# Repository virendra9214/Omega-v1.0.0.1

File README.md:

Omega – ESP32 STEM Controller Board

Omega is an ESP32-based controller board created by  VIRENDRA SINGH SHEKHAWAT from India to make STEM education, robotics, and IoT more accessible.  
It combines Wi-Fi, BLE, sensor inputs, motor drivers, and easy expansion in one compact design — perfect for classrooms, tinkering labs, hobbyists, and competitions.

---

Key Features
- MCU: ESP32-WROOM-32E (Dual-core, Wi-Fi + BLE)
- Programming: Arduino IDE, MicroPython, block-based IDE (PictoBlox-style)
- Motors & Servos:
  - 2× TB6612FNG motor drivers (up to 4 12v motors)
  - 3× Servo headers (5 V PWM)
- Sensors Supported:
  - Ultrasonic, IR, MPU6050 IMU, Color sensor, DHT, analog/digital expansion
- Outputs:
  - WS2812B RGB LED
  - PAM8403 speaker amplifier
- Connectivity:
  - I²C, UART, PWM, ADC, DAC via JST connectors
- Power:
  - Auto USB-C / 12 V barrel jack switching (FDN340P MOSFET)
  - Onboard 5 V & 3.3 V regulation with fuse, diodes, ESD protection

---

 Educational Value
- Free for students, hobbyists, and individual educators.
- Supports hands-on STEM learning: electronics, coding, IoT, robotics
- Beginner-friendly with block-based coding
- Expandable for advanced learners with C++/Python
- Supports Indian education initiatives (NEP 2020, Skill India, Atal Tinkering Labs)

---

Example Projects
- IoT-based smart irrigation system  
- Accident detection and car safety module  
- Line follower / obstacle avoiding robots  
- BLE remote-controlled car  
- Classroom experiments: data logging, servo control, LED patterns  

---

 Repository Contents
- `/Production` → KiCad schematic, PCB, BOM  
- `/firmware` → Arduino / MicroPython example codes  
- `/datasheets` → Datasheets, pin mapping, tutorials  
- `/codes` → Ready-to-run projects for students and testing after production 

---

License
This project is released under the Omega Educational License (OEL-1.0).  
-  Free for education, research, and personal use  
-  Commercial use requires a paid license from the creator  
-  Significant design modifications and redistributions are not allowed  
youtube link:https://www.youtube.com/@LEARN_OMEGA
📩 Contact: virendrasinghshekhawat786@gmail.com for commercial licensing inquiries.

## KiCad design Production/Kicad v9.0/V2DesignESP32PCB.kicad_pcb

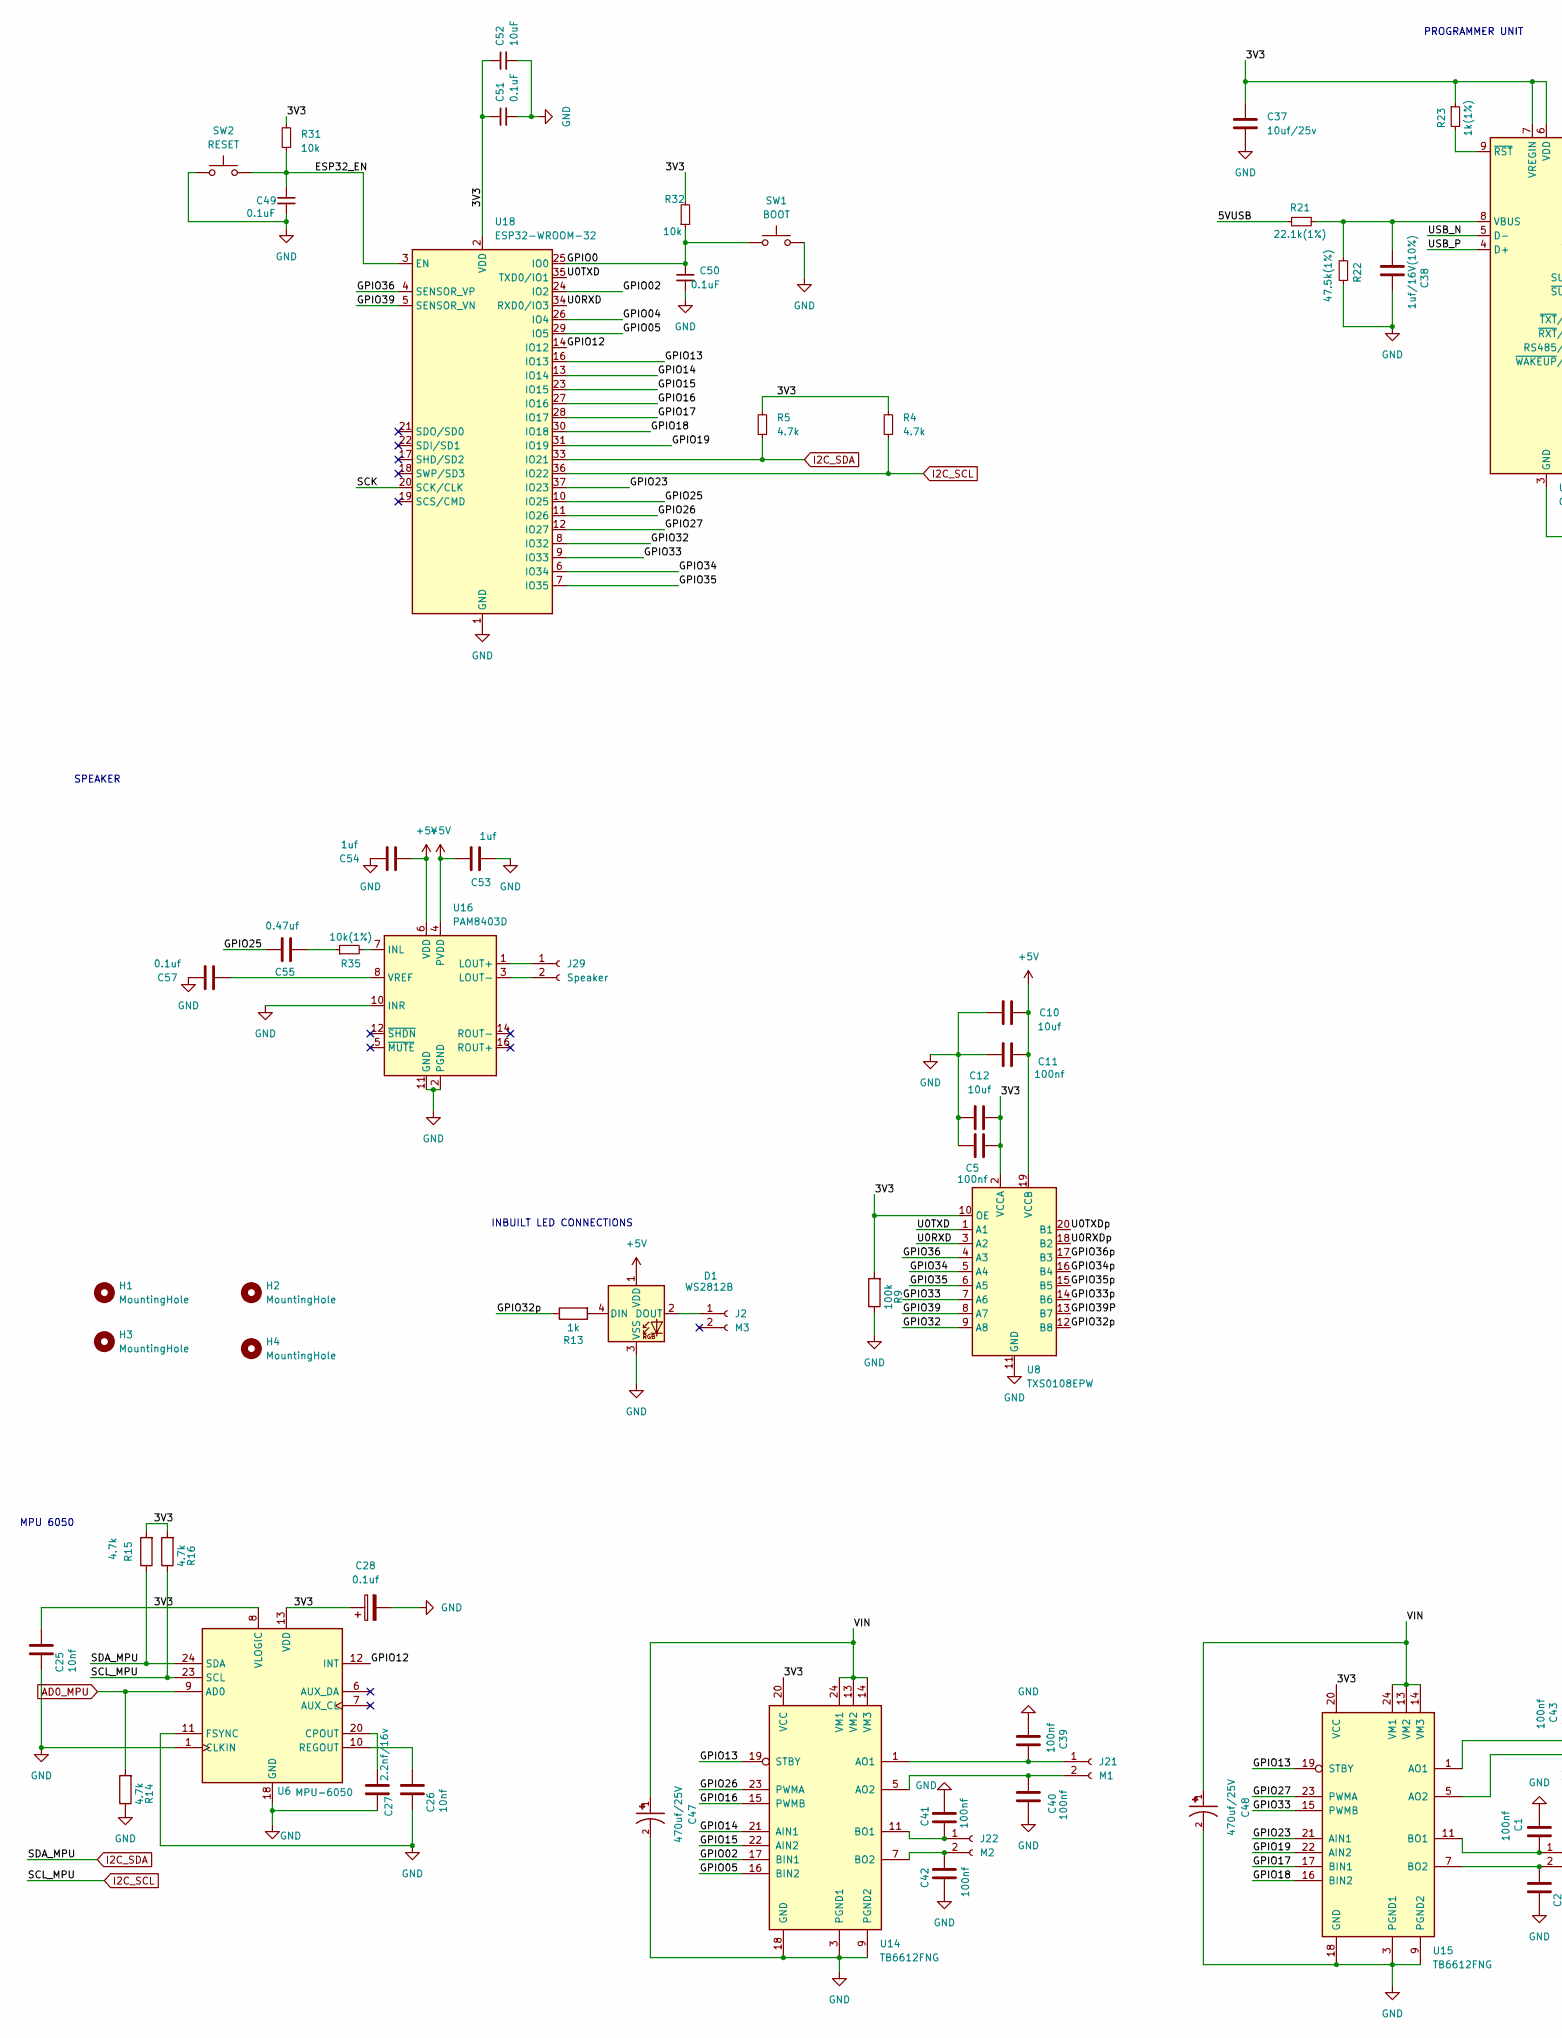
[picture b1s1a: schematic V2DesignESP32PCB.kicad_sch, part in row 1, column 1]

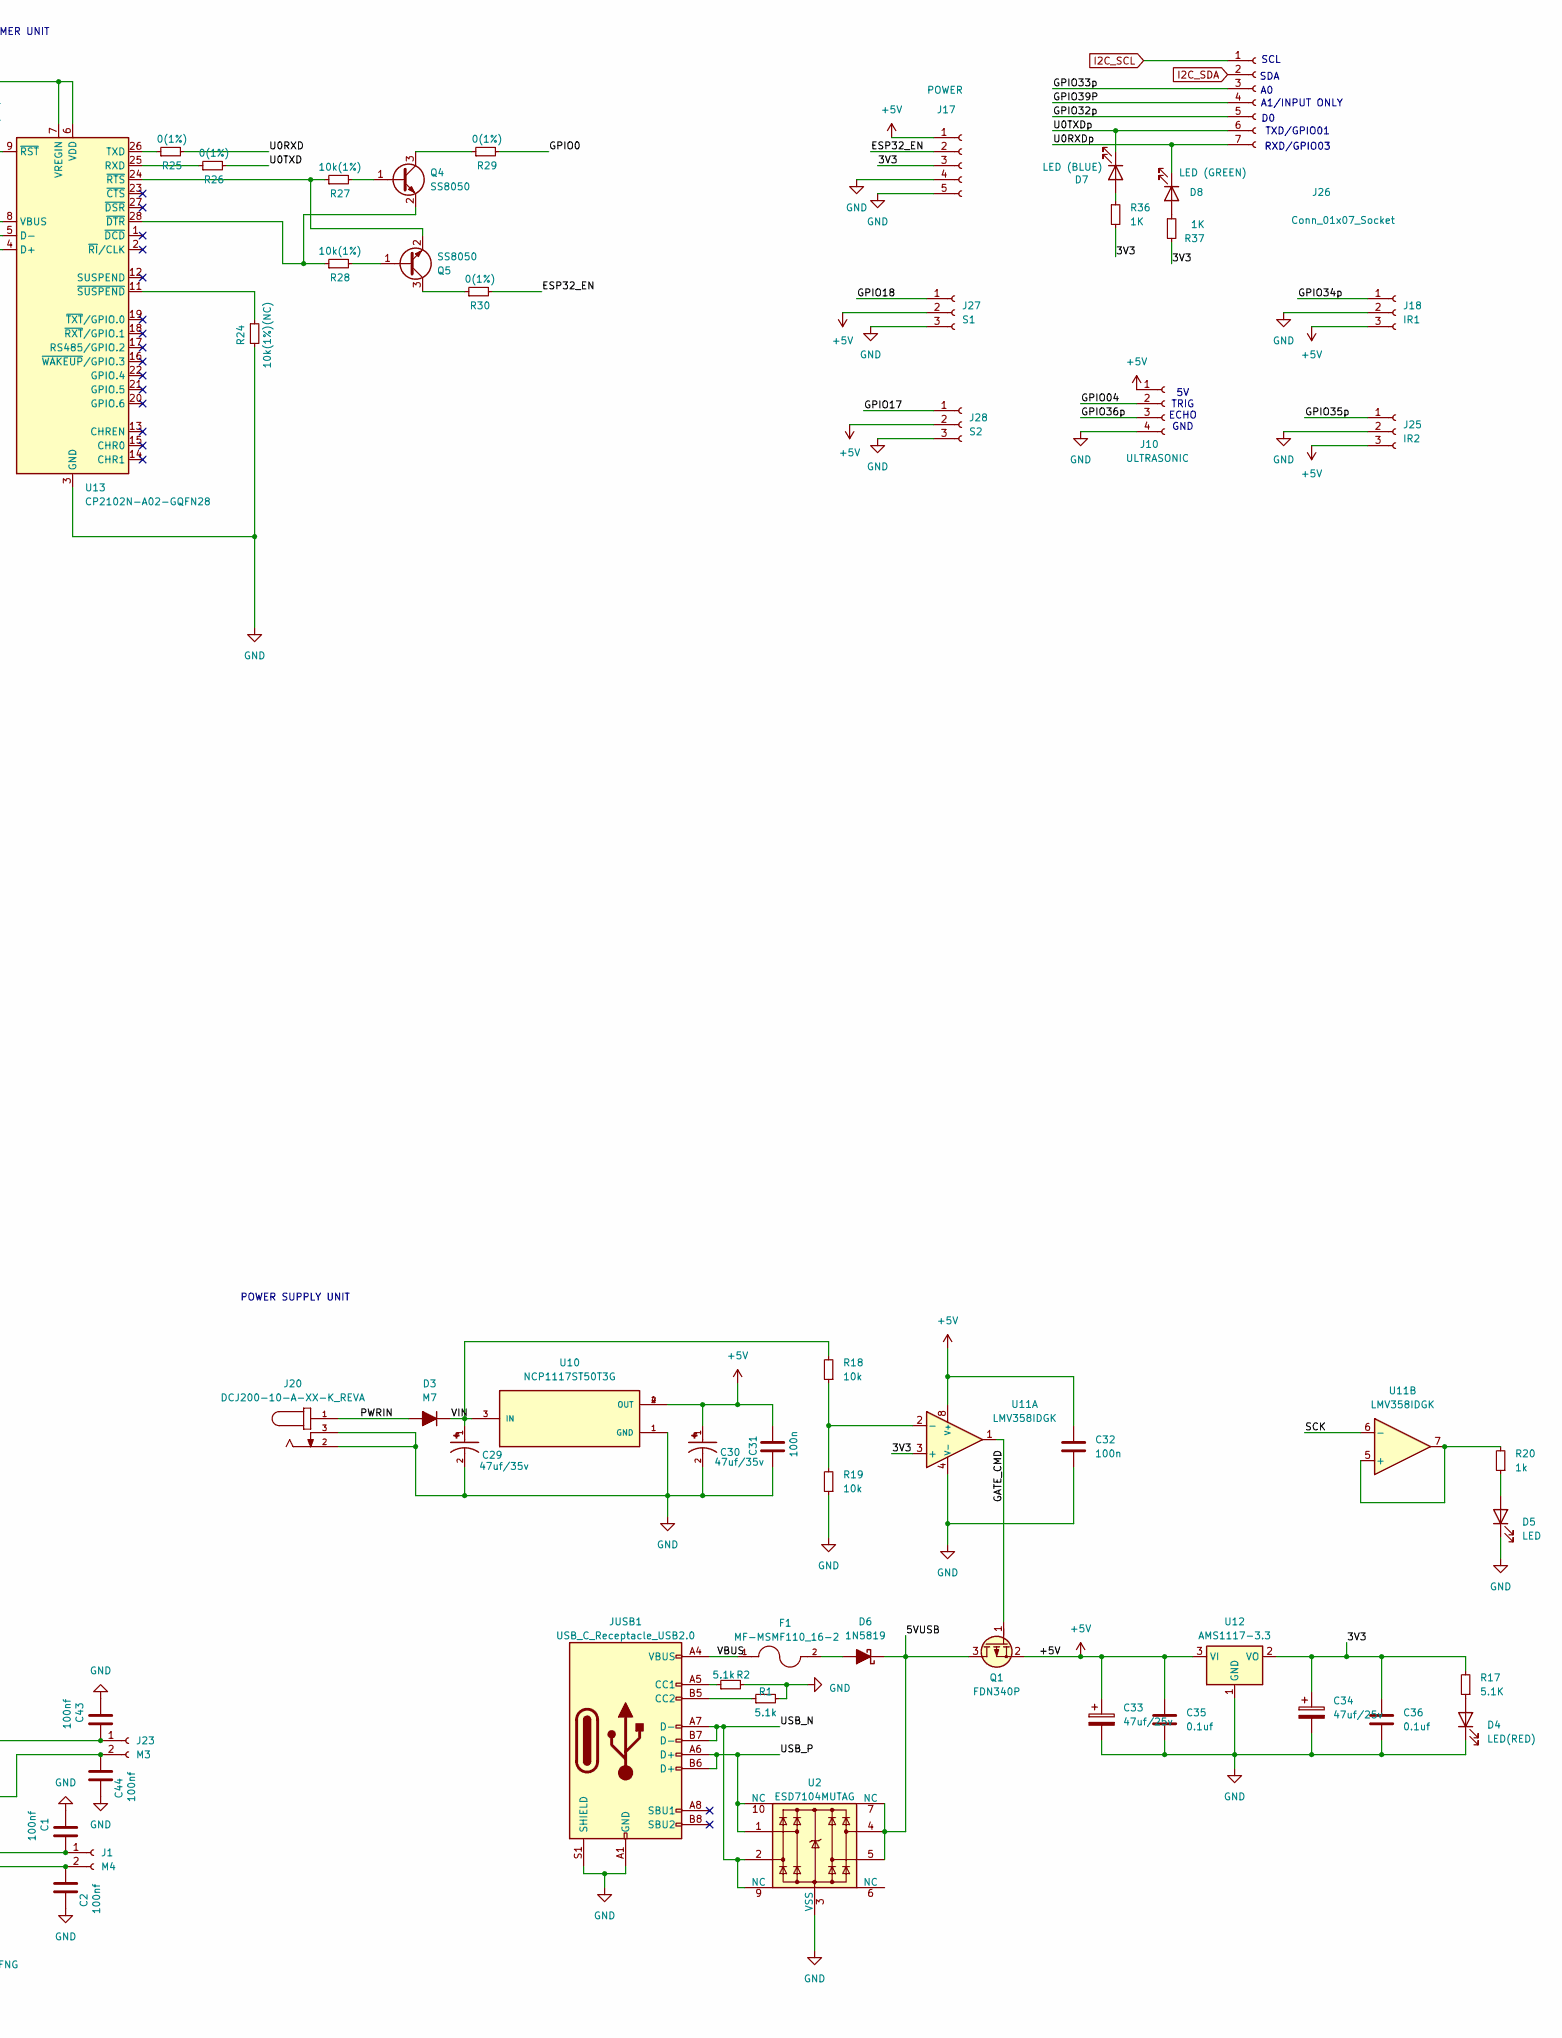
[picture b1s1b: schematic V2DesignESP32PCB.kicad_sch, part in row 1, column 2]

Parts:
C1, C2, C5, C11, C39, C40, C41, C42, C43, C44: 100nf; C_0805_2012Metric
C10, C12: 10uf; C_0805_2012Metric
C25, C26: 10nf; C_0603_1608Metric
C27: 2.2nf/16v; C_0603_1608Metric
C28: 0.1uf; C_0603_1608Metric
C29, C30: 47uf/35v; CAP_EEETC1V470V; PARTREV 10-Oct-19
C31, C32: 100n; C_0805_2012Metric
C33, C34: 47uf/25v; C_0805_2012Metric
C35, C36, C57: 0.1uf; C_0805_2012Metric
C37: 10uf/25v; C_0603_1608Metric
C38: 1uf/16V(10%); C_0603_1608Metric
C47, C48: 470uf/25V; CAP_EEETC1V470V; PARTREV 10-Oct-19
C49, C50, C51: 0.1uF; C_0603_1608Metric; MANUFECTURER PART NUMBER ${ITEM_NUMBER}
C52: 10uF; C_0603_1608Metric; MANUFECTURER PART NUMBER ${ITEM_NUMBER}
C53, C54: 1uf; C_0805_2012Metric
C55: 0.47uf; C_0805_2012Metric
D1: WS2812B; LED_WS2812B_PLCC4_5.0x5.0mm_P3.2mm; MANUFECTURER PART NUMBER ${ITEM_NUMBER}
D3: M7; D_SMA
D4: LED(RED); LED_0805_2012Metric; MANUFECTURER PART NUMBER ${ITEM_NUMBER}
D5: LED; LED_0805_2012Metric; MANUFECTURER PART NUMBER ${ITEM_NUMBER}
D6: 1N5819; D_SOD-123
D7: LED (BLUE); LED_0805_2012Metric; MANUFECTURER PART NUMBER ${ITEM_NUMBER}
D8: LED (GREEN); LED_0805_2012Metric; MANUFECTURER PART NUMBER ${ITEM_NUMBER}
F1: MF-MSMF110_16-2; FUSER_MF-MSMF110_16-2
H1, H2, H3, H4: MountingHole; MountingHole_4mm
J1: M4; MANUFECTURER PART NUMBER ${ITEM_NUMBER}
J2, J23: M3; JST_EH_B2B-EH-A_1x02_P2.50mm_Vertical; MANUFECTURER PART NUMBER ${ITEM_NUMBER}
J10: ULTRASONIC; JST_EH_B4B-EH-A_1x04_P2.50mm_Vertical; MANUFECTURER PART NUMBER ${ITEM_NUMBER}
J17: POWER; JST_EH_B5B-EH-A_1x05_P2.50mm_Vertical
J18: IR1; JST_EH_B3B-EH-A_1x03_P2.50mm_Vertical; MANUFECTURER PART NUMBER ${ITEM_NUMBER}
J20: DCJ200-10-A-XX-K_REVA; BarrelJack_GCT_DCJ200-10-A_Horizontal; PARTREV A
J21: M1; JST_EH_B2B-EH-A_1x02_P2.50mm_Vertical; MANUFECTURER PART NUMBER ${ITEM_NUMBER}
J22: M2; JST_EH_B2B-EH-A_1x02_P2.50mm_Vertical; MANUFECTURER PART NUMBER ${ITEM_NUMBER}
J25: IR2; JST_EH_B3B-EH-A_1x03_P2.50mm_Vertical; MANUFECTURER PART NUMBER ${ITEM_NUMBER}
J26: Conn_01x07_Socket; JST_EH_B7B-EH-A_1x07_P2.50mm_Vertical
J27: S1; JST_EH_B3B-EH-A_1x03_P2.50mm_Vertical; MANUFECTURER PART NUMBER ${ITEM_NUMBER}
J28: S2; JST_EH_B3B-EH-A_1x03_P2.50mm_Vertical; MANUFECTURER PART NUMBER ${ITEM_NUMBER}
J29: Speaker; JST_EH_B2B-EH-A_1x02_P2.50mm_Vertical; MANUFECTURER PART NUMBER ${ITEM_NUMBER}
JUSB1: USB_C_Receptacle_USB2.0; USB_C_Receptacle_GCT_USB4105-xx-A_16P_TopMnt_Horizontal; MANUFECTURER PART NUMBER ${ITEM_NUMBER}
Q1: FDN340P; SuperSOT-3
Q4, Q5: SS8050; SOT-23
R1, R2: 5.1k; R_0805_2012Metric; MANUFECTURER PART NUMBER ${ITEM_NUMBER}
R4, R5: 4.7k; R_0603_1608Metric; MANUFECTURER PART NUMBER ${ITEM_NUMBER}
R9: 100k; R_0603_1608Metric
R13: 1k; R_0603_1608Metric
R14, R15, R16: 4.7k; R_0603_1608Metric
R17: 5.1K; R_0805_2012Metric; MANUFECTURER PART NUMBER ${ITEM_NUMBER}
R18, R19: 10k; R_0805_2012Metric; MANUFECTURER PART NUMBER ${ITEM_NUMBER}
R20: 1k; R_0805_2012Metric; MANUFECTURER PART NUMBER ${ITEM_NUMBER}
R21: 22.1k(1%); R_0603_1608Metric; MANUFECTURER PART NUMBER ${ITEM_NUMBER}
R22: 47.5k(1%); R_0603_1608Metric; MANUFECTURER PART NUMBER ${ITEM_NUMBER}
R23: 1k(1%); R_0603_1608Metric; MANUFECTURER PART NUMBER ${ITEM_NUMBER}
R24: 10k(1%)(NC); R_0603_1608Metric; MANUFECTURER PART NUMBER ${ITEM_NUMBER}
R25, R26, R29, R30: 0(1%); R_0603_1608Metric; MANUFECTURER PART NUMBER ${ITEM_NUMBER}
R27, R28: 10k(1%); R_0603_1608Metric; MANUFECTURER PART NUMBER ${ITEM_NUMBER}
R31, R32: 10k; R_0603_1608Metric; MANUFECTURER PART NUMBER ${ITEM_NUMBER}
R35: 10k(1%); R_0805_2012Metric; MANUFECTURER PART NUMBER ${ITEM_NUMBER}
R36, R37: 1K; R_0805_2012Metric; MANUFECTURER PART NUMBER ${ITEM_NUMBER}
SW1: BOOT; SW_SPST_PTS810
SW2: RESET; SW_SPST_PTS810
U2: ESD7104MUTAG; Diodes_UDFN-10_1.0x2.5mm_P0.5mm; MANUFECTURER PART NUMBER ${ITEM_NUMBER}
U6: MPU-6050; InvenSense_QFN-24_4x4mm_P0.5mm
U8: TXS0108EPW; TSSOP-20_4.4x6.5mm_P0.65mm
U10: NCP1117ST50T3G; SOT230P700X180-4N; DigiKey_Part_Number NCP1117ST50T3GOSTR-ND
U11: LMV358IDGK; MSOP-8_3x3mm_P0.65mm
U12: AMS1117-3.3; SOT-223-3_TabPin2
U13: CP2102N-A02-GQFN28; QFN-28-1EP_5x5mm_P0.5mm_EP3.35x3.35mm
U14, U15: TB6612FNG; SSOP-24_5.3x8.2mm_P0.65mm
U16: PAM8403D; SOP-16_3.9x9.9mm_P1.27mm
U18: ESP32-WROOM-32

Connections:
+5V: C10.2, C11.1, C30.1, C31.1, C32.1, C33.1, C35.1, C53.2, C54.1, D1.1 (VDD), J10.1, J17.1, J18.3, J25.3, J27.2, J28.2, Q1.2 (S), U8.19 (VCCB), U10.2 (OUT), U10.4 (OUT), U11.8 (V+), U12.3 (VI), U16.4 (PVDD), U16.6 (VDD), U16.13 (PVDD)
/3V3: C5.1, C12.2, C25.1, C28.1, C34.1, C36.1, C37.1, C51.1, C52.1, J17.3, R4.2, R5.2, R9.2, R15.2, R16.2, R17.2, R23.1, R31.2, R32.2, R36.2, R37.2, U6.8 (VLOGIC), U6.13 (VDD), U8.2 (VCCA), U8.10 (OE), U11.3 (+), U12.2 (VO), U13.6 (VDD), U13.7 (VREGIN), U14.20 (VCC), U15.20 (VCC), U18.2 (VDD)
/5VUSB: D6.1 (K), Q1.3 (D), R21.2, U2.4, U2.5, U2.7 (NC)
/ESP32_EN: C49.1, J17.2, R30.2, R31.1, SW2.2, U18.3 (EN)
/GATE_CMD: Q1.1 (G), U11.1
/GPIO0: C50.1, R29.2, R32.1, SW1.1, U18.25 (IO0)
/GPIO02: U14.17 (BIN1), U18.24 (IO2)
/GPIO04: J10.2, U18.26 (IO4)
/GPIO05: U14.16 (BIN2), U18.29 (IO5)
/GPIO12: U6.12 (INT), U18.14 (IO12)
/GPIO13: U14.19 (STBY), U15.19 (STBY), U18.16 (IO13)
/GPIO14: U14.21 (AIN1), U18.13 (IO14)
/GPIO15: U14.22 (AIN2), U18.23 (IO15)
/GPIO16: U14.15 (PWMB), U18.27 (IO16)
/GPIO17: J28.1, U15.17 (BIN1), U18.28 (IO17)
/GPIO18: J27.1, U15.16 (BIN2), U18.30 (IO18)
/GPIO19: U15.22 (AIN2), U18.31 (IO19)
/GPIO23: U15.21 (AIN1), U18.37 (IO23)
/GPIO25: C55.2, U18.10 (IO25)
/GPIO26: U14.23 (PWMA), U18.11 (IO26)
/GPIO27: U15.23 (PWMA), U18.12 (IO27)
/GPIO32: U8.9 (A8), U18.8 (IO32)
/GPIO32p: J26.5, R13.1, U8.12 (B8)
/GPIO33: U8.7 (A6), U15.15 (PWMB), U18.9 (IO33)
/GPIO33p: J26.3, U8.14 (B6)
/GPIO34: U8.5 (A4), U18.6 (IO34)
/GPIO34p: J18.1, U8.16 (B4)
/GPIO35: U8.6 (A5), U18.7 (IO35)
/GPIO35p: J25.1, U8.15 (B5)
/GPIO36: U8.4 (A3), U18.4 (SENSOR_VP)
/GPIO36p: J10.3, U8.17 (B3)
/GPIO39: U8.8 (A7), U18.5 (SENSOR_VN)
/GPIO39P: J26.4, U8.13 (B7)
/PWRIN: D3.2 (A), J20.1
/SCK: U11.6 (-), U18.20 (SCK/CLK)
/U0RXD: R25.2, U8.3 (A2), U18.34 (RXD0/IO3)
/U0RXDp: D8.1 (K), J26.7, U8.18 (B2)
/U0TXD: R26.2, U8.1 (A1), U18.35 (TXD0/IO1)
/U0TXDp: D7.1 (K), J26.6, U8.20 (B1)
/USB_N: JUSB1.A7 (D-), JUSB1.B7 (D-), U2.2, U2.9 (NC), U13.5 (D-)
/USB_P: JUSB1.A6 (D+), JUSB1.B6 (D+), U2.1, U2.10 (NC), U13.4 (D+)
/VBUS: F1.1, JUSB1.A4 (VBUS), JUSB1.A9 (VBUS), JUSB1.B4 (VBUS), JUSB1.B9 (VBUS)
/VIN: C29.1, C47.1, C48.1, D3.1 (K), R18.2, U10.3 (IN), U14.13 (VM2), U14.14 (VM3), U14.24 (VM1), U15.13 (VM2), U15.14 (VM3), U15.24 (VM1)
AD0_MPU: R14.2, U6.9 (AD0)
GND: C1.2, C2.2, C5.2, C10.1, C11.2, C12.1, C25.2, C26.2, C27.2, C28.2, C29.2, C30.2, C31.2, C32.2, C33.2, C34.2, C35.2, C36.2, C37.2, C38.2, C39.2, C40.2, C41.2, C42.2, C43.2, C44.2, C47.2, C48.2, C49.2, C50.2, C51.2, C52.2, C53.1, C54.2, C57.2, D1.3 (VSS), D4.1 (K), D5.1 (K), J10.4, J17.4, J17.5, J18.2, J20.2, J20.3, J25.2, J27.3, J28.3, JUSB1.A1 (GND), JUSB1.A12 (GND), JUSB1.B1 (GND), JUSB1.B12 (GND), JUSB1.S1 (SHIELD), R1.2, R2.2, R9.1, R14.1, R19.1, R22.1, R24.2, SW1.2, SW2.1, U2.3 (VSS), U2.8 (VSS), U6.1 (CLKIN), U6.11 (FSYNC), U6.18 (GND), U8.11 (GND), U10.1 (GND), U11.4 (V-), U12.1 (GND), U13.3 (GND), U13.29 (GND), U14.3 (PGND1), U14.4 (PGND1), U14.9 (PGND2), U14.10 (PGND2), U14.18 (GND), U15.3 (PGND1), U15.4 (PGND1), U15.9 (PGND2), U15.10 (PGND2), U15.18 (GND), U16.2 (PGND), U16.10 (INR), U16.11 (GND), U16.15 (PGND), U18.1 (GND), U18.15 (GND), U18.38 (GND), U18.39 (GND)
I2C_SCL: J26.1, R4.1, R16.1, U6.23 (SCL), U18.36 (IO22)
I2C_SDA: J26.2, R5.1, R15.1, U6.24 (SDA), U18.33 (IO21)
unnamed: C55.1, R35.1
unnamed: D1.4 (DIN), R13.2
unnamed: D1.2 (DOUT), J2.1
unnamed: D4.2 (A), R17.1
unnamed: D5.2 (A), R20.1
unnamed: D6.2 (A), F1.2
unnamed: D7.2 (A), R36.1
unnamed: D8.2 (A), R37.1
unnamed: C1.1, J1.1, U15.11 (BO1), U15.12 (BO1)
unnamed: C2.1, J1.2, U15.7 (BO2), U15.8 (BO2)
unnamed: C39.1, J21.1, U14.1 (AO1), U14.2 (AO1)
unnamed: C40.1, J21.2, U14.5 (AO2), U14.6 (AO2)
unnamed: C41.1, J22.1, U14.11 (BO1), U14.12 (BO1)
unnamed: C42.1, J22.2, U14.7 (BO2), U14.8 (BO2)
unnamed: C43.1, J23.1, U15.1 (AO1), U15.2 (AO1)
unnamed: C44.1, J23.2, U15.5 (AO2), U15.6 (AO2)
unnamed: J29.1, U16.1 (LOUT+)
unnamed: J29.2, U16.3 (LOUT-)
unnamed: JUSB1.A5 (CC1), R2.1
unnamed: JUSB1.B5 (CC2), R1.1
unnamed: Q4.1 (B), R27.2
unnamed: Q4.3 (C), R29.1
unnamed: Q4.2 (E), R28.1, U13.28 (~DTR)
unnamed: Q5.1 (B), R28.2
unnamed: Q5.3 (C), R30.1
unnamed: Q5.2 (E), R27.1, U13.24 (~RTS)
unnamed: C27.1, U6.20 (CPOUT)
unnamed: C26.1, U6.10 (REGOUT)
unnamed: R18.1, R19.2, U11.2 (-)
unnamed: R20.2, U11.5 (+), U11.7
unnamed: R26.1, U13.25 (RXD)
unnamed: R25.1, U13.26 (TXD)
unnamed: C38.1, R21.1, R22.2, U13.8 (VBUS)
unnamed: R23.2, U13.9 (~RST)
unnamed: R24.1, U13.11 (~SUSPEND)
unnamed: R35.2, U16.7 (INL)
unnamed: C57.1, U16.8 (VREF)

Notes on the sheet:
PROGRAMMER UNIT
SCL
MPU 6050
INBUILT LED CONNECTIONS
A1/INPUT ONLY
SDA
5V TRIG ECHO GND
POWER SUPPLY UNIT
RXD/GPIO03
SPEAKER
TXD/GPIO01

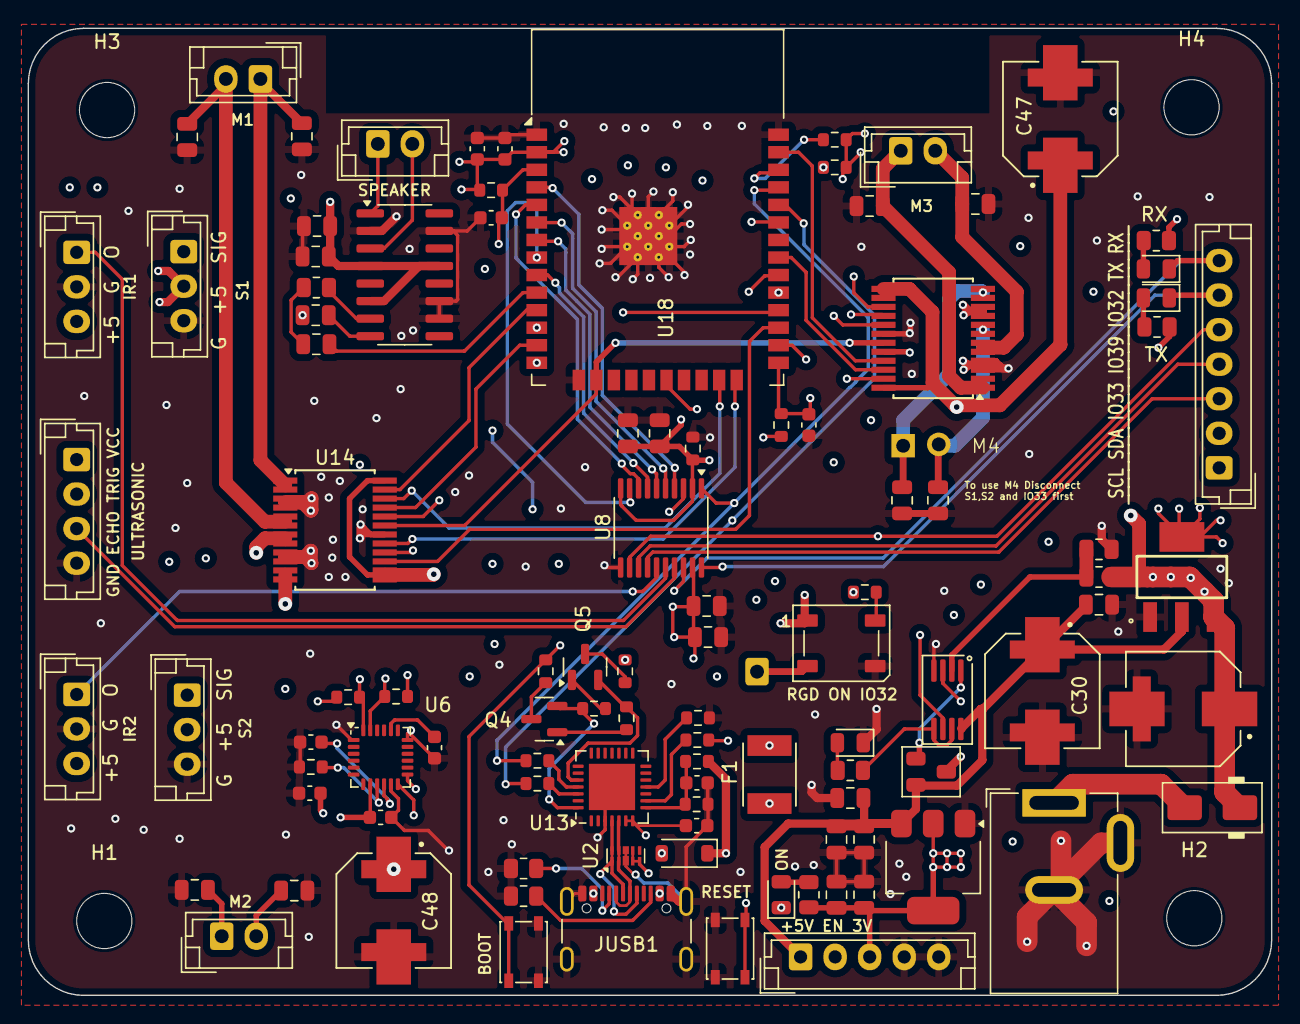
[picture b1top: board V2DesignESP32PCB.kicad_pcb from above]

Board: 4 copper layers, 90.0 x 70.0 mm, 105 parts (0 on the bottom side), 83 nets.

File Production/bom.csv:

Designator,Footprint,Quantity,Value,LCSC Part #
"_3, _2, ",,3,,
"C1, C11, C2, C39, C40, C41, C42, C43, C44, C5",0805,10,100nf,
"C10, C12",0805,2,10uf,
"C25, C26",0603,2,10nf,
C27,0603,1,2.2nf/16v,
"C28, C49, C50, C51",0603,4,0.1uf,
"C29, C30",CAP_EEETC1V470V,2,47uf/35v,
"C31, C32",0805,2,100n,
"C33, C34",0805,2,47uf/25v,
"C35, C36, C57",0805,3,0.1uf,
C37,0603,1,10uf/25v,
C38,0603,1,1uf/16V(10%),
"C47, C48",CAP_EEETC1V470V,2,470uf/25V,
C52,0603,1,10uF,
"C53, C54",0805,2,1uf,
C55,0805,1,0.47uf,
D1,LED_WS2812B_PLCC4_5.0x5.0mm_P3.2mm,1,WS2812B,
D3,D_SMA,1,M7,
D4,0805,1,LED(RED),
D5,0805,1,LED,
D6,D_SOD-123,1,1N5819,
D7,0805,1,LED (BLUE),
D8,0805,1,LED (GREEN),
F1,FUSER_MF-MSMF110_16-2,1,MF-MSMF110_16-2,
J10,JST_EH_B4B-EH-A_1x04_P2.50mm_Vertical,1,ULTRASONIC,
J17,JST_EH_B5B-EH-A_1x05_P2.50mm_Vertical,1,POWER,
J18,JST_EH_B3B-EH-A_1x03_P2.50mm_Vertical,1,IR1,
J20,BarrelJack_GCT_DCJ200-10-A_Horizontal,1,DCJ200-10-A-XX-K_REVA,
J21,JST_EH_B2B-EH-A_1x02_P2.50mm_Vertical,1,M1,
J22,JST_EH_B2B-EH-A_1x02_P2.50mm_Vertical,1,M2,
J23,JST_EH_B2B-EH-A_1x02_P2.50mm_Vertical,1,M3,
J25,JST_EH_B3B-EH-A_1x03_P2.50mm_Vertical,1,IR2,
J26,JST_EH_B7B-EH-A_1x07_P2.50mm_Vertical,1,Conn_01x07_Socket,
J27,JST_EH_B3B-EH-A_1x03_P2.50mm_Vertical,1,S1,
J28,JST_EH_B3B-EH-A_1x03_P2.50mm_Vertical,1,S2,
J29,JST_EH_B2B-EH-A_1x02_P2.50mm_Vertical,1,Speaker,
JUSB1,USB_C_Receptacle_GCT_USB4105-xx-A_16P_TopMnt_Horizontal,1,USB_C_Receptacle_USB2.0,
Q1,SuperSOT-3,1,FDN340P,
"Q4, Q5",SOT-23,2,SS8050,
"R1, R17, R2",0805,3,5.1k,
R13,0603,1,1k,
"R14, R15, R16, R4, R5",0603,5,4.7k,
"R18, R19",0805,2,10k,
"R20, R36, R37",0805,3,1k,
R21,0603,1,22.1k(1%),
R22,0603,1,47.5k(1%),
R23,0603,1,1k(1%),
R24,0603,1,10k(1%)(NC),
"R25, R26, R29, R30",0603,4,0(1%),
"R27, R28",0603,2,10k(1%),
"R31, R32",0603,2,10k,
R35,0805,1,10k(1%),
R9,0603,1,100k,
SW1,SW_SPST_PTS810,1,BOOT,
SW2,SW_SPST_PTS810,1,RESET,
U10,SOT230P700X180-4N,1,NCP1117ST50T3G,
U11,MSOP-8_3x3mm_P0.65mm,1,LMV358IDGK,
U12,SOT-223-3_TabPin2,1,AMS1117-3.3,
U13,QFN-28-1EP_5x5mm_P0.5mm_EP3.35x3.35mm,1,CP2102N-A02-GQFN28,
"U14, U15",SSOP-24_5.3x8.2mm_P0.65mm,2,TB6612FNG,
U16,SOP-16_3.9x9.9mm_P1.27mm,1,PAM8403D,
U18,ESP32-WROOM-32,1,ESP32-WROOM-32,
U2,Diodes_UDFN-10_1.0x2.5mm_P0.5mm,1,ESD7104MUTAG,
U6,InvenSense_QFN-24_4x4mm_P0.5mm,1,MPU-6050,
U8,TSSOP-20_4.4x6.5mm_P0.65mm,1,TXS0108EPW,

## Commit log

2025-09-10 Create hi
2025-09-10 Rename hi to Firmware
2025-09-10 Create Production Note
2025-09-10 Create test
2025-09-10 Create lib
2025-09-10 Create sheets
2025-09-10 Create Obstacle avoiding robot

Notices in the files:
Production/Kicad v9.0/V2DesignESP32PCB.kicad_pcb:
© 2025 VIRENDRA SINGH SHEKHAWAT All rights reserved.
